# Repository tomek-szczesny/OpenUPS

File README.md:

# OpenUPS

A universal and versatile high power SBC UPS

## Introduction

**This is a work in progress repository**

More up-to-date information available on Odroid forum:

[Open source UPS design - ODROID](https://forum.odroid.com/viewtopic.php?f=55&t=46481)

License:

### Install
```
  git clone https://github.com/tomek-szczesny/OpenUPS.git

```

### OpenUPS Features:
-  Multi SBC support
-  Wide Input Voltage Range: 12V - 24V
-  Multiple Output Voltages: 5V, 12V, Programmable (0-24V) or Vin repeater,
-  Dual SATA power ports, supports 3.5" HDDs as well,
-  Dual 12V Fan ports with PWM control and RPM monitoring,
-  I2C Configuration and Reporting, incl. Battery Voltage, Current
-  3D-printable Custom Cases
   - Drive Bay Case Mount
   - Standalone Case
-  Expandable 3S1P Battery Capacity
-  18650, 20700 or 21700 Cell Support
-  Easy Battery Maintenance

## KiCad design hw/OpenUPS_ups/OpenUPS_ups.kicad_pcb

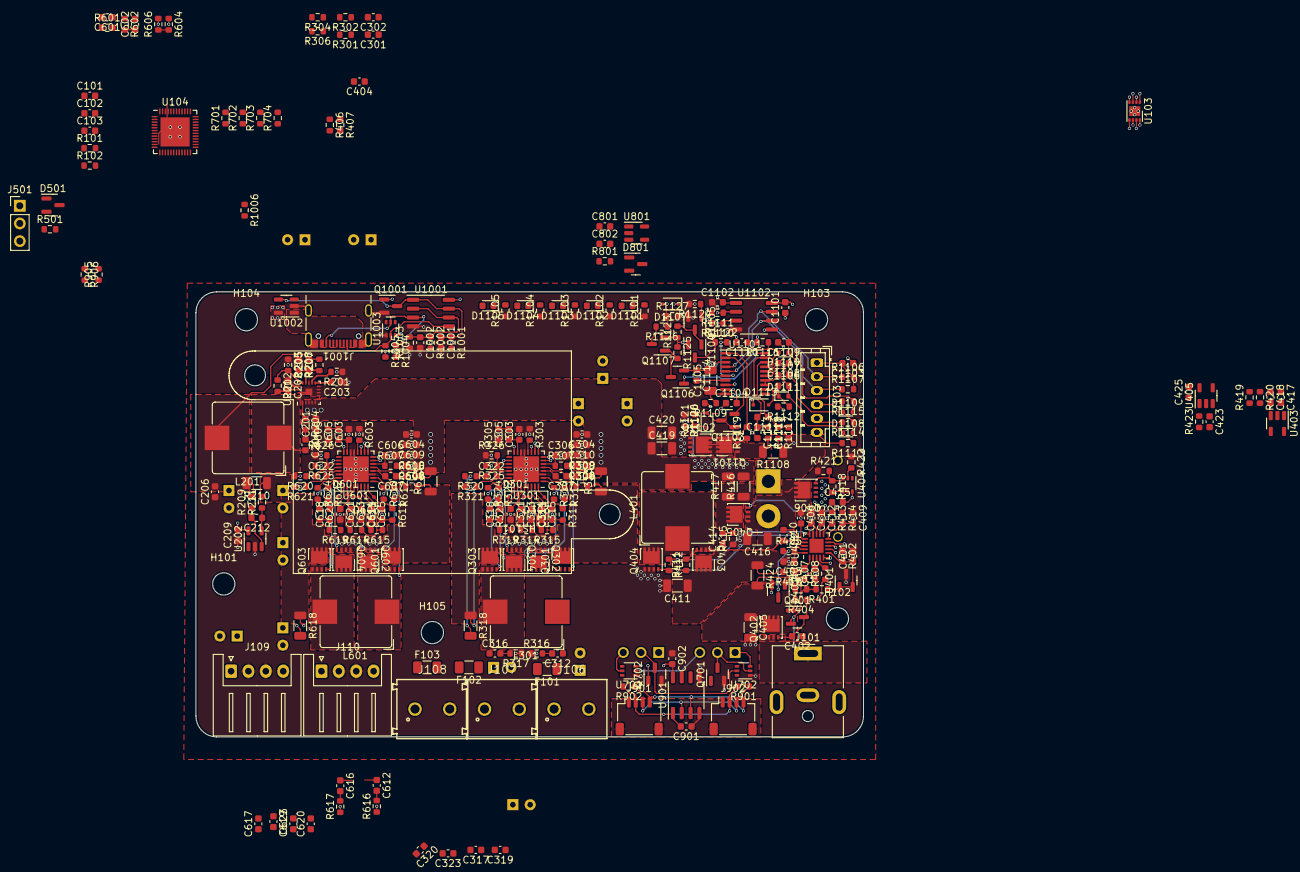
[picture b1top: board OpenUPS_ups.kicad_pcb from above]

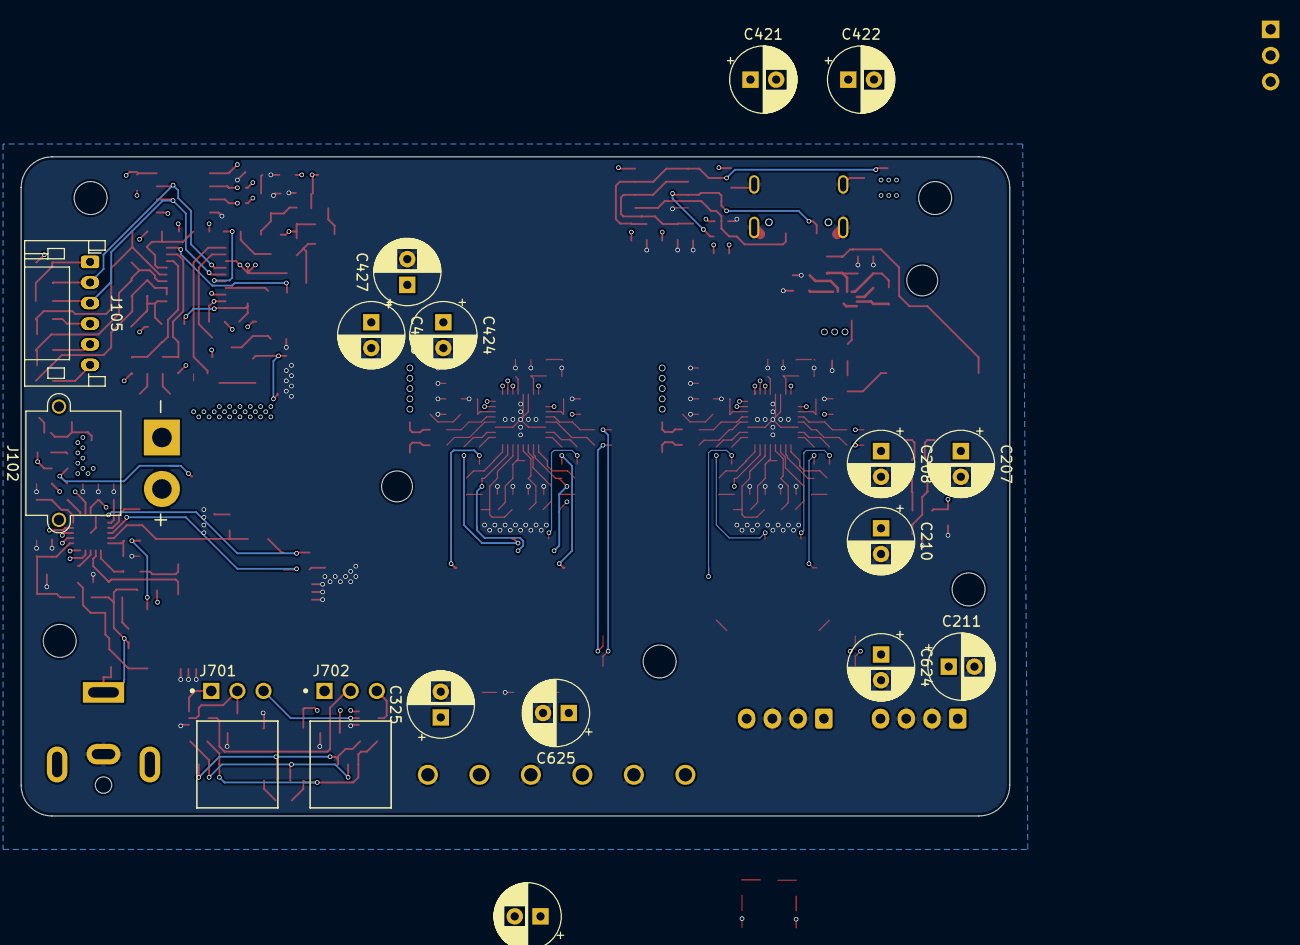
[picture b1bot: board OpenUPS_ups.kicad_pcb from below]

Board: 4 copper layers, 96.0 x 64.0 mm, 332 parts (17 on the bottom side), 182 nets.

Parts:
C101, C102, C103, C206, C209, C311, C318, C417, C425, C611, C618: 100n 10V; C_0603_1608Metric
C201, C204: 100n 50V; C_0603_1608Metric
C202, C802: 1u; C_0603_1608Metric
C203, C312, C316, C414, C612, C616, C1001: NM; C_0603_1608Metric
C205: 100p; C_0603_1608Metric
C207, C208, C210, C211: 16ZLG47MEFC6.3X7; CP_Radial_D6.3mm_P2.50mm
C212: 10u; C_0603_1608Metric
C301, C302, C307, C322, C601, C602, C607, C622, C1002: 10n; C_0603_1608Metric
C303, C603: 10p; C_0603_1608Metric
C304, C308, C309, C310, C317, C319, C320, C323, C604, C608, C609, C610, C617, C619, C620, C623: 10u 35V; C_0603_1608Metric
C305, C605: 1n5; C_0603_1608Metric
C306, C321, C606, C621: 100n 35V; C_0603_1608Metric
C313, C314, C315, C613, C614, C615: 1u 6.3V; C_0603_1608Metric
C324, C325, C421, C422, C424, C426, C427, C624, C625: 25ZLG47MEFC6.3X7; CP_Radial_D6.3mm_P2.50mm
C401: 100p 25V; C_0603_1608Metric
C402, C415: 10n 16V; C_0603_1608Metric
C403, C406, C801: 1u 25V; C_0603_1608Metric
C404: 4n7 6.3V; C_0603_1608Metric
C405: 22u 25V; C_1206_3216Metric
C407, C412, C413: 100n 25V; C_0603_1608Metric
C408, C409, C1104, C1114: 1u 16V; C_0603_1608Metric
C410: 100n 16V; C_0603_1608Metric
C411: 10u 25V; C_1206_3216Metric
C416, C1105: 10u 16V; C_1206_3216Metric
C418: 1n 10V; C_0603_1608Metric
C419, C420: 22u 16V; C_1206_3216Metric
C423, C901, C902, C1101, C1102, C1111, C1112, C1113: 100n; C_0603_1608Metric
C1103: 4u7 6.3V; C_0603_1608Metric
C1106, C1107, C1108, C1109, C1110: 1u 10V; C_0603_1608Metric
D301, D303, D601, D603, D1106, D1107, D1113: BAT54J; D_SOD-323F
D401, D801: BAT54C; SOT-23
D501: BAT54; SOT-23
D1101, D1102, D1103, D1104: G; LED_0603_1608Metric
D1105: R; LED_0603_1608Metric
D1108, D1109, D1110, D1111: ESD5Z5V0-DIO; D_SOD-523
F101, F102: C1T-4; Fuse_1206_3216Metric
F103: C1T-5; Fuse_1206_3216Metric
H101, H102, H103, H104, H105: MountingHole; MountingHole_3.2mm_M3_DIN965
HS101: Heatsink; C4_heatsink
J101: Barrel Jack; BarrelJack_CUI_PJ-063AH_Horizontal
J102: XT30PW-M; AMASS_XT30PW-M_1x02_P2.50mm_Horizontal
J103: B6B-PH-K_1x06; JST_PH_B6B-PH-K_1x06_P2.00mm_Vertical
J105: S6B-PH-K_1x06; JST_PH_S6B-PH-K_1x06_P2.00mm_Horizontal
J106, J107, J108: Screw Terminal; 691213710002
J109, J110: JST XH; JST_XH_S4B-XH-A_1x04_P2.50mm_Horizontal
J501: Conn_01x03; PinHeader_1x03_P2.54mm_Vertical
J701, J702: 0022053031; Molex-22-05-3031-MFG
J901, J902: Qwiic; JST_SH_SM04B-SRSS-TB_1x04-1MP_P1.00mm_Horizontal
J1001: USB4105-GF-A; USB_C_Receptacle_GCT_USB4105-xx-A_16P_TopMnt_Horizontal
L201, L401: SRP1038C-2R2M; L_Bourns_SRP1038C_10.0x10.0mm
L301, L601: SRP1038C-3R3M; L_Bourns_SRP1038C_10.0x10.0mm
Q301, Q302, Q303, Q304, Q402, Q403, Q404, Q405, Q601, Q602, Q603, Q604, Q1101, Q1102: AON7534; DFN 3x3 MOSFET
Q401, Q701, Q702, Q1001, Q1105, Q1106: 2N7002; SOT-23
Q406: AON7423; DFN 3x3 MOSFET
Q1103, Q1104, Q1107: BSS84; SOT-23
R101, R102, R901, R902, R905, R906, R1106, R1107: 3k3; R_0603_1608Metric
R201, R301, R302, R304, R306, R406, R407, R601, R602, R604, R606, R701, R702, R703, R704, R801, R1001, R1004, R1005, R1006, R1126, R1127: 10k; R_0603_1608Metric
R202: 330k; R_0603_1608Metric
R203, R208: 15k; R_0603_1608Metric
R204, R307, R311, R312, R319, R322, R323, R411, R412, R607, R611, R612, R619, R622, R623: 0R; R_0603_1608Metric
R207: 110k; R_0603_1608Metric
R209, R211, R310, R324, R610, R624: 3R3; R_0603_1608Metric
R210: 2mR 1206; R_1206_3216Metric
R303, R603: ?; R_0603_1608Metric
R305, R605: 20k; R_0603_1608Metric
R308, R309, R314, R320, R321, R405, R410, R608, R609, R614, R620, R621: 10R; R_0603_1608Metric
R313, R318, R613, R618: 5m 1W; R_1206_3216Metric
R315, R615: 1R; R_0603_1608Metric
R316, R317, R415, R418, R616, R617, R1110, R1111: NM; R_0603_1608Metric
R325, R401, R625, R1002: 18k; R_0603_1608Metric
R326, R626: 2k; R_0603_1608Metric
R402: 4k7; R_0603_1608Metric
R403: 3M; R_0603_1608Metric
R404, R1119, R1120, R1121: 1M; R_0603_1608Metric
R408: 5k1; R_0603_1608Metric
R413, R414: 510R; R_0603_1608Metric
R416, R417: 10m 1/2W; R_1206_3216Metric
R419: 1M2; R_0603_1608Metric
R420: 300k; R_0603_1608Metric
R421, R422, R1123, R1124, R1125: 100k; R_0603_1608Metric
R423, R1101, R1102, R1103, R1104, R1105: 1k; R_0603_1608Metric
R424: 20m 1/2W; R_1206_3216Metric
R501: 470; R_0603_1608Metric
R1003: 22k; R_0603_1608Metric
R1108: Rsns; R_1206_3216Metric
R1109: 100R; R_0603_1608Metric
R1112, R1113, R1114, R1115, R1116: 51R; R_0603_1608Metric
R1117, R1118: 100; R_0603_1608Metric
R1122: 68k; R_0603_1608Metric
U103: LM75BTP,147; SON-8-1EP_3x2mm_P0.5mm_EP1.4x1.6mm
U104: AVR64DB48x-x6LX; QFN-48-1EP_6x6mm_P0.4mm_EP4.2x4.2mm
U201: TPS51397A; Texas-VQFN-HR-20_EP_3x3_Pitch0.45mm
U202: INA180A3; SOT-23-5
U301, U601: NCP81599; QFN-32-1EP_5x5mm_P0.5mm_EP3.7x3.7mm
U401: NCP431; SOT-23
U402: BD99950; QFN-20-1EP_3.5x3.5mm_P0.5mm_EP2x2mm
U403: MCP6001R; SOT-23-5
U404: DZDH0401DW; SOT-363_SC-70-6
U405: INA180A1; SOT-23-5
U701, U702, U1003: NUP2301MW6T1G; SOT-363_SC-70-6
U801: AP7383-33W5; SOT-23-5
U901, U1102: π220N31; SO-8_3.9x4.9mm_P1.27mm
U1001: MCP6547; SO-8_3.9x4.9mm_P1.27mm
U1002: AP22814BW5; SOT-23-5
U1101: BQ76920PW; TSSOP-20_4.4x6.5mm_P0.65mm

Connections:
+3.3VA: C101.1, C102.1, C103.1, C209.2, C417.2, C425.2, C802.2, C902.2, C1102.2, D1107.1 (K), R101.2, R102.2, R306.2, R406.2, R407.2, R606.2, R701.2, R702.2, R703.2, R704.2, R905.2, R906.2, R1110.2, R1111.2, U103.8 (+Vs), U104.14 (VDDIO2), U104.28 (AVDD), U104.42 (VDD), U202.5 (V+), U403.2 (V+), U405.5 (V+), U701.3, U801.5 (VOUT), U901.8 (VDD2), U1102.1 (VDD1)
+5V: C207.1, C208.1, C210.1, C211.1, F103.1, J109.1, J110.1, R210.1, R211.2, R1001.2, R1002.2, R1004.2, R1005.2, U1001.8 (V+), U1002.5 (IN), U1003.3
+12V: C617.1, C619.1, C620.1, C623.1, C624.1, C625.1, F102.1, J109.4, J110.4, J701.1, J702.1, R618.2, R619.2, R620.2, R625.2, U702.3
+AdjV: C317.1, C319.1, C320.1, C323.1, C324.1, C325.1, F101.1, R318.2, R319.2, R320.2, R325.2
+BATT: C415.2, C416.1, C1104.2, J102.2, Q405.1 (S), Q405.2 (S), Q405.3 (S), Q406.5 (D), Q406.6 (D), Q406.7 (D), Q406.8 (D), Q1104.2 (S), Q1107.2 (S), R414.1, R419.2, R1109.2, R1112.2, R1123.1, R1125.1, U404.6 (D), U1101.9 (REGSRC)
-BATT: C1101.1, C1103.1, C1104.1, C1105.2, C1109.2, C1110.2, C1112.1, C1113.2, C1114.1, J102.1, Q1103.1 (G), Q1106.2 (S), R1108.1, R1116.2, R1117.2, U1101.3 (VSS), U1102.5 (GND2)
/12V Buck_Boost/VDRV: C614.1, D601.2 (A), D603.2 (A), R615.2, U601.29 (VDRV)
/Adj_Buck_Boost/VDRV: C314.1, D301.2 (A), D303.2 (A), R315.2, U301.29 (VDRV)
/Aux Power Supplies/EN2: C411.1, D801.1, Q403.5 (D), Q403.6 (D), Q403.7 (D), Q403.8 (D), R410.2, R424.1
/BMS/BMS_SCL: J103.3, J105.3, R1107.1, U1101.5 (SCL), U1102.6 (SCL2)
/BMS/BMS_SDA: J103.2, J105.2, R1106.1, U1101.4 (SDA), U1102.7 (SDA2)
/BMS/TS: R1122.2, U1101.6 (TS1)
/BMS_ALERT: D1107.2 (A), R1126.1, R1127.1
/BMS_WKUP: Q1105.1 (G), R1124.1
/B_ACOK: R407.1, U402.5 (ACOK)
/B_BATTRM: R406.1, U402.4 (BATTRM)
/B_I: C423.2, R423.1
/B_IOUT: C404.2, U402.7 (IOUT)
/B_U: U403.1, U403.4 (-)
/Bat_Charger/B_SRN: C412.2, Q405.5 (D), Q405.6 (D), Q405.7 (D), Q405.8 (D), R416.1, R417.1, U402.12 (SRN), U405.3 (+)
/Ext. I2C Interface/XI2C_GND: C901.1, J901.1, J901.MP (MountPin), J902.1, J902.MP (MountPin), U901.4 (GND1)
/Ext. I2C Interface/XI2C_SCL: J901.4, J902.4, R902.1, U901.3 (SCL1)
/Ext. I2C Interface/XI2C_SDA: J901.3, J902.3, R901.1, U901.2 (SDA1)
/Ext. I2C Interface/XI2C_VCC: C901.2, J901.2, J902.2, R901.2, R902.2, U901.1 (VDD1)
/F_PWM0: Q701.1 (G), R701.1
/F_PWM1: Q702.1 (G), R702.1
/F_Tach0: J701.3, R703.1, U701.2
/F_Tach1: J702.3, R704.1, U701.5
/I2C_B_SCL: R1110.1, U104.37 (PF3), U1102.3 (SCL1)
/I2C_B_SDA: R1111.1, U104.36 (PF2), U1102.2 (SDA1)
/I2C_E_SCL: R905.1, U104.13 (PC3), U901.6 (SCL2)
/I2C_E_SDA: R906.1, U104.12 (PC2), U901.7 (SDA2)
/I2C_I_SCL: R102.1, U103.2 (SCL), U104.47 (PA3), U301.10 (SCL), U402.9 (SCL), U601.10 (SCL)
/I2C_I_SDA: R101.1, U103.1 (SDA), U104.46 (PA2), U301.9 (SDA), U402.8 (SDA), U601.9 (SDA)
/UPDI: D501.1 (A), J501.3, U104.41 (UPDI)
/USB_FORCE: Q1001.1 (G), R1006.2
/V5_EN: R201.2, U201.12 (EN)
/V5_Imon: U104.26 (PD6), U202.1
/V12_CS1: C602.1, R602.2, U104.24 (PD4), U601.7 (CS1)
/V12_CS2: C601.1, R601.2, U104.25 (PD5), U601.18 (CS2)
/V12_EN: R604.2, R606.1, U601.16 (EN)
/VC1: J103.4, J105.4, R1115.2
/VC2: J103.5, J105.5, R1114.2
/VC3: J103.6, J105.6, R1113.2
/Vadj_CS1: C302.1, R302.2, U104.22 (PD2), U301.7 (CS1)
/Vadj_CS2: C301.1, R301.2, U104.23 (PD3), U301.18 (CS2)
/Vadj_EN: R304.2, R306.1, U301.16 (EN)
GND: C101.2, C102.2, C103.2, C201.1, C202.1, C203.1, C206.1, C207.2, C208.2, C209.1, C210.2, C211.2, C301.2, C302.2, C303.2, C304.2, C306.2, C308.2, C309.2, C310.2, C313.2, C314.2, C315.2, C317.2, C319.2, C320.2, C321.2, C323.2, C324.2, C325.2, C401.2, C403.2, C404.1, C405.2, C406.1, C407.1, C409.1, C411.2, C412.1, C413.1, C416.2, C417.1, C418.1, C419.2, C420.2, C421.2, C422.2, C423.1, C424.2, C425.1, C426.2, C427.2, C601.2, C602.2, C603.2, C604.2, C606.2, C608.2, C609.2, C610.2, C613.2, C614.2, C615.2, C617.2, C619.2, C620.2, C621.2, C623.2, C624.2, C625.2, C801.1, C802.1, C902.1, C1001.2, C1002.2, C1102.1, J101.2, J106.2, J107.2, J108.2, J109.2, J109.3, J110.2, J110.3, J501.1, J1001.A1 (GND), J1001.A12 (GND), J1001.B1 (GND), J1001.B12 (GND), J1001.S1 (SHIELD), Q302.1 (S), Q302.2 (S), Q302.3 (S), Q304.1 (S), Q304.2 (S), Q304.3 (S), Q404.1 (S), Q404.2 (S), Q404.3 (S), Q602.1 (S), Q602.2 (S), Q602.3 (S), Q604.1 (S), Q604.2 (S), Q604.3 (S), Q701.2 (S), Q702.2 (S), Q1001.2 (S), Q1102.1 (S), Q1102.2 (S), Q1102.3 (S), Q1105.2 (S), R201.1, R203.1, R208.1, R301.1, R302.1, R303.1, R304.1, R305.1, R316.1, R317.1, R326.1, R402.1, R415.1, R420.1, R421.1, R422.1, R601.1, R602.1, R603.1, R604.1, R605.1, R616.1, R617.1, R626.1, R801.1, R1003.1, R1006.1, R1101.1, R1102.1, R1103.1, R1104.1, R1105.1, R1120.1, R1124.2, R1127.2, U103.4 (GND), U103.5 (A2), U103.6 (A1), U103.7 (A0), U104.15 (GND), U104.29 (AGND), U104.43 (GND), U104.49 (GND), U201.7 (PGND), U201.8 (PGND), U201.9 (PGOOD), U201.10 (NC), U201.13 (AGND), U201.16 (NC), U201.18 (PGND), U201.21 (PGND), U202.2 (GND), U301.3 (PGND1), U301.13 (AGND), U301.14 (AGND), U301.22 (PGND2), U301.33 (THPAD), U401.3 (A), U402.14 (GND), U402.21 (PAD), U403.5 (V-), U405.2 (GND), U601.3 (PGND1), U601.13 (AGND), U601.14 (AGND), U601.22 (PGND2), U601.33 (THPAD), U701.1, U702.1, U801.2 (GND), U801.4 (NC), U901.5 (GND2), U1001.4 (V-), U1002.2 (GND), U1003.1, U1102.4 (GND1)
unnamed: C204.1, R204.2
unnamed: C204.2, L201.1, U201.6 (SW), U201.19 (SW), U201.20 (SW)
unnamed: C205.2, C206.2, L201.2, R207.2, R209.2, R210.2
unnamed: C305.2, R305.2
unnamed: C311.1, R311.2
unnamed: C312.2, R316.2
unnamed: C316.2, R317.2
unnamed: C318.1, R323.2
unnamed: C414.2, R415.2
unnamed: C605.2, R605.2
unnamed: C611.1, R611.2
unnamed: C612.2, R616.2
unnamed: C616.2, R617.2
unnamed: C618.1, R623.2
unnamed: D301.1 (K), R323.1, U301.25 (BST2)
unnamed: D303.1 (K), R311.1, U301.32 (BST1)
unnamed: D401.3, R405.1
unnamed: D501.3 (K), R501.1
unnamed: D601.1 (K), R623.1, U601.25 (BST2)
unnamed: D603.1 (K), R611.1, U601.32 (BST1)
unnamed: D1101.1 (K), R1101.2
unnamed: D1102.1 (K), R1102.2
unnamed: D1103.1 (K), R1103.2
unnamed: D1104.1 (K), R1104.2
unnamed: D1105.1 (K), R1105.2
unnamed: D1106.2 (A), Q1103.3 (D), R1121.2
unnamed: D1106.1 (K), Q1102.4 (G), R1120.2, R1121.1
unnamed: C1106.2, C1107.1, D1108.1 (A1), D1111.2 (A2), R1113.1, U1101.13 (VC4), U1101.14 (VC3)
unnamed: C1107.2, C1108.1, D1108.2 (A2), D1109.1 (A1), R1114.1, U1101.15 (VC2)
unnamed: C1108.2, C1109.1, D1109.2 (A2), D1110.1 (A1), R1115.1, U1101.16 (VC1)
unnamed: C1110.1, D1110.2 (A2), R1116.1, U1101.17 (VC0)
unnamed: C1106.1, D1111.1 (A1), D1113.2 (A), R1112.1, U1101.12 (VC5)
unnamed: C1105.1, D1113.1 (K), R1109.1, U1101.10 (BAT)
unnamed: F101.2, J106.1
unnamed: F102.2, J107.1
unnamed: F103.2, J108.1
unnamed: J501.2, R501.2
unnamed: J701.2, Q701.3 (D), U702.2
unnamed: J702.2, Q702.3 (D), U702.5
unnamed: J1001.A5 (CC1), R1005.1, U1001.5 (+), U1003.2
unnamed: J1001.B5 (CC2), R1004.1, U1001.3 (+), U1003.5
unnamed: Q301.5 (D), Q301.6 (D), Q301.7 (D), Q301.8 (D), R309.2, R313.1
unnamed: Q301.4 (G), R310.2
unnamed: Q302.4 (G), R312.2
unnamed: Q303.5 (D), Q303.6 (D), Q303.7 (D), Q303.8 (D), R318.1, R321.2
unnamed: Q303.4 (G), R322.2
unnamed: Q304.4 (G), R324.2
unnamed: C402.2, Q401.3 (D), Q402.4 (G), R404.1, R408.1
unnamed: Q401.1 (G), R403.1, R404.2
unnamed: Q403.4 (G), R411.2
unnamed: Q404.4 (G), R412.2
unnamed: C415.1, Q405.4 (G), R413.1
unnamed: Q406.4 (G), R418.1, R421.2, U404.3 (BIAS)
unnamed: Q601.5 (D), Q601.6 (D), Q601.7 (D), Q601.8 (D), R609.2, R613.1
unnamed: Q601.4 (G), R610.2
unnamed: Q602.4 (G), R612.2
unnamed: Q603.5 (D), Q603.6 (D), Q603.7 (D), Q603.8 (D), R618.1, R621.2
unnamed: Q603.4 (G), R622.2
unnamed: Q604.4 (G), R624.2
unnamed: C1001.1, Q1001.3 (D), R1001.1, U1001.1, U1001.7, U1002.4 (~EN)
unnamed: Q1101.5 (D), Q1101.6 (D), Q1101.7 (D), Q1101.8 (D), Q1102.5 (D), Q1102.6 (D), Q1102.7 (D), Q1102.8 (D)
unnamed: Q1101.4 (G), R1119.2, U1101.1 (DSG)
unnamed: Q1101.1 (S), Q1101.2 (S), Q1101.3 (S), R1108.2, R1118.2, R1119.1
unnamed: Q1103.2 (S), U1101.2 (CHG)
unnamed: Q1104.3 (D), R1122.1
unnamed: Q1104.1 (G), Q1105.3 (D), R1123.2
unnamed: Q1106.3 (D), Q1107.1 (G), R1125.2
unnamed: Q1106.1 (G), U1101.20 (ALERT)
unnamed: Q1107.3 (D), R1126.2
unnamed: R423.2, U405.1
unnamed: R204.1, U201.1 (BST)
unnamed: C205.1, R207.1, R208.2, U201.14 (FB)
unnamed: R202.1, R203.2, U201.15 (MODE)
unnamed: C203.2, U201.11 (SS)
unnamed: C202.2, R202.2, U201.17 (VCC)
unnamed: C212.2, R209.1, U202.3 (+)
unnamed: C212.1, R211.1, U202.4 (-)
unnamed: R303.2, U301.12 (ADDR)
unnamed: C303.1, C305.1, U301.15 (COMP)
unnamed: C315.1, R314.1, R315.1, U301.30 (VCC)
unnamed: C313.1, R314.2, U301.28 (VCCD)
unnamed: C307.2, R309.1, U301.4 (CSN1)
unnamed: C307.1, R308.1, U301.5 (CSP1)
unnamed: R310.1, U301.1 (HSG1)
unnamed: R312.1, U301.2 (LSG1)
unnamed: C306.1, R307.1, U301.6 (V1)
unnamed: C311.2, C312.1, L301.1, Q301.1 (S), Q301.2 (S), Q301.3 (S), Q302.5 (D), Q302.6 (D), Q302.7 (D), Q302.8 (D), U301.31 (VSW1)
unnamed: C322.1, R320.1, U301.20 (CSN2)
unnamed: C322.2, R321.1, U301.21 (CSP2)
unnamed: R325.1, R326.2, U301.19 (FB)
unnamed: R322.1, U301.24 (HSG2)
unnamed: R324.1, U301.23 (LSG2)
unnamed: C321.1, R319.1, U301.27 (V2)
unnamed: C316.1, C318.2, L301.2, Q303.1 (S), Q303.2 (S), Q303.3 (S), Q304.5 (D), Q304.6 (D), Q304.7 (D), Q304.8 (D), U301.26 (VSW2)
unnamed: C401.1, R401.1, R402.2, U401.1 (REF), U401.2 (K), U402.6 (ACDET)
unnamed: R408.2, U402.3 (ACGATE)
unnamed: C408.2, R410.1, U402.1 (ACN)
unnamed: C405.1, C407.2, C408.1, Q402.5 (D), Q402.6 (D), Q402.7 (D), Q402.8 (D), R424.2, U402.2 (ACP)
unnamed: C409.2, R414.2, U402.10 (BATT)
unnamed: R413.2, U402.11 (BGATE)
unnamed: C410.1, U402.17 (BOOT)
unnamed: R411.1, U402.18 (HDRV)
unnamed: R412.1, U402.15 (LDRV)
unnamed: C410.2, C414.1, L401.1, Q403.1 (S), Q403.2 (S), Q403.3 (S), Q404.5 (D), Q404.6 (D), Q404.7 (D), Q404.8 (D), U402.19 (PHASE)
unnamed: C406.2, U402.16 (REGN)
unnamed: C403.1, R405.2, U402.20 (VCC)
unnamed: C418.2, R419.1, R420.2, U403.3 (+)
unnamed: R422.2, U404.2 (REF)
unnamed: R603.2, U601.12 (ADDR)
unnamed: C603.1, C605.1, U601.15 (COMP)
unnamed: C615.1, R614.1, R615.1, U601.30 (VCC)
unnamed: C613.1, R614.2, U601.28 (VCCD)
unnamed: C607.2, R609.1, U601.4 (CSN1)
unnamed: C607.1, R608.1, U601.5 (CSP1)
unnamed: R610.1, U601.1 (HSG1)
unnamed: R612.1, U601.2 (LSG1)
unnamed: C606.1, R607.1, U601.6 (V1)
unnamed: C611.2, C612.1, L601.1, Q601.1 (S), Q601.2 (S), Q601.3 (S), Q602.5 (D), Q602.6 (D), Q602.7 (D), Q602.8 (D), U601.31 (VSW1)
unnamed: C622.1, R620.1, U601.20 (CSN2)
unnamed: C622.2, R621.1, U601.21 (CSP2)
unnamed: R625.1, R626.2, U601.19 (FB)
unnamed: R622.1, U601.24 (HSG2)
unnamed: R624.1, U601.23 (LSG2)
unnamed: C621.1, R619.1, U601.27 (V2)
unnamed: C616.1, C618.2, L601.2, Q603.1 (S), Q603.2 (S), Q603.3 (S), Q604.5 (D), Q604.6 (D), Q604.7 (D), Q604.8 (D), U601.26 (VSW2)
unnamed: D801.3, R801.2, U801.3 (EN)
unnamed: C1002.1, R1002.1, R1003.2, U1001.2 (-), U1001.6 (-)
unnamed: J1001.A4 (VBUS), J1001.A9 (VBUS), J1001.B4 (VBUS), J1001.B9 (VBUS), U1002.1 (OUT)
unnamed: C1114.2, U1101.7 (CAP1)
unnamed: C1111.2, C1113.1, R1118.1, U1101.19 (SRN)
unnamed: C1111.1, C1112.2, R1117.1, U1101.18 (SRP)
VBMS: C1101.2, C1103.2, J103.1, J105.1, R1106.2, R1107.2, U1101.8 (REGOUT), U1102.8 (VDD2)
Vin: C402.1, D401.1, J101.1, Q401.2 (S), Q402.1 (S), Q402.2 (S), Q402.3 (S), R401.2, R403.2
Vsys: C201.2, C304.1, C308.1, C309.1, C310.1, C413.2, C419.1, C420.1, C421.1, C422.1, C424.1, C426.1, C427.1, C604.1, C608.1, C609.1, C610.1, C801.2, D401.2, L401.2, Q406.1 (S), Q406.2 (S), Q406.3 (S), R307.2, R308.2, R313.2, R416.2, R417.2, R418.2, R607.2, R608.2, R613.2, U201.2 (VIN), U201.3 (VIN), U201.4 (VIN), U201.5 (VIN), U402.13 (SRP), U404.4 (S), U405.4 (-), U801.1 (VIN)

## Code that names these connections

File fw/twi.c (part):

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        // set twi pin mux
        switch(twi_bus->pins) {
            case TWI_PINS_ALT1 :
                PORTMUX_TWIROUTEA = PORTMUX_TWI0_ALT1_gc;   /* PA2, PA3, PC6, PC7 */
                PORTA_DIRSET = PIN2_bm | PIN3_bm;
                if(twi_bus->pullup == true) PORTA_PINCONFIG = PORT_PULLUPEN_bm;
                PORTA_PINCTRLUPD = PIN2_bm | PIN3_bm;
            case TWI_PINS_ALT2 :
                PORTMUX_TWIROUTEA = PORTMUX_TWI0_ALT2_gc;   /* PC2, PC3, PC6, PC7 */
                PORTC_DIRSET = PIN2_bm | PIN3_bm;
                if(twi_bus->pullup == true) PORTC_PINCONFIG = PORT_PULLUPEN_bm;
                PORTC_PINCTRLUPD = PIN2_bm | PIN3_bm;
            case TWI_PINS_DEFAULT :
                PORTMUX_TWIROUTEA = PORTMUX_TWI0_DEFAULT_gc;    /* PA2, PA3, PC2, PC3 */
                PORTA_DIRSET = PIN2_bm | PIN3_bm;
                if(twi_bus->pullup == true) PORTA_PINCONFIG = PORT_PULLUPEN_bm;
                PORTA_PINCTRLUPD = PIN2_bm | PIN3_bm;
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        // set twi pin mux
        switch(twi_bus->pins) {
            case TWI_PINS_ALT1 :
                PORTMUX_TWIROUTEA = PORTMUX_TWI1_DEFAULT_gc;   /* PF2, PF3 */
                PORTF_DIRSET = PIN2_bm | PIN3_bm;
                if(twi_bus->pullup == true) PORTF_PINCONFIG = PORT_PULLUPEN_bm;
                PORTF_PINCTRLUPD = PIN2_bm | PIN3_bm;
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                if(twi_bus->pullup == true) PORTB_PINCONFIG = PORT_PULLUPEN_bm;
                PORTB_PINCTRLUPD = PIN2_bm | PIN3_bm;
            case TWI_PINS_DEFAULT :
                PORTMUX_TWIROUTEA = PORTMUX_TWI1_DEFAULT_gc;    /* PF2, PF3, PB2, PB3 */
                PORTF_DIRSET = PIN2_bm | PIN3_bm;
                if(twi_bus->pullup == true) PORTF_PINCONFIG = PORT_PULLUPEN_bm;
                PORTF_PINCTRLUPD = PIN2_bm | PIN3_bm;
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
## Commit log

2023-04-21 Initial KiCAD commits
2023-04-21 More cleanups and stuff
2023-04-22 Fixed ground symbols
2023-04-22 Preliminary battery charger circuit
2023-04-22 initial commit of PCB models, updated readme.md
2023-04-22 corrected readme.md
2023-04-23 added drivebay case
2023-04-23 created terminal block screw openings and annotation
2023-04-23 Secondary blocks design
2023-04-23 code cleanup and xt60 creation
2023-04-24 mini case work
2023-04-24 more mini case refinement
2023-04-24 updated image
2023-04-24 Update OpenUPS features list
2023-04-24 Added Ideal Diode ORing solution
2023-04-24 Change minimum input voltage back to 12V
2023-04-25 Upgraded battery charger with synchronous HB Driver
2023-04-26 Battery charger HB driver changed to NCP5901
2023-04-28 created xt30 components and changed mini case to use xt30
2023-04-28 platter view created, swapped i2c and fan, more code cleanup
2023-04-28 work on 3s1p battery case
2023-04-28 work on 3s2p battery case
2023-04-28 A buildable AVR FW template
2023-04-28 Deps cleanup
2023-04-30 4th generation battery charger
2023-05-01 increased space for fan connectors
2023-05-01 External I2C isolator
2023-05-02 customizer gui added
2023-05-02 corrected staggered battery clip placement
2023-05-02 Work on Buck Boosts
2023-05-02 Work on 5V; EN pins taken care of.
2023-05-03 Added ports and fuses
2023-05-05 Issue #17
2023-05-05 Issue #13, USB-C output, at last!
2023-05-06 Issue #20: replaced AVR with 48-pin TQFP
2023-05-06 Issue #16: Added LED indicators
2023-05-07 increased 3s1p battery pcb size, adjusted drivebay case
2023-05-08 more work for battery pcb size increase and case pillars.
2023-05-09 Issue #24 5th generation charger (may need some tuning)
2023-05-10 xt30 orientation change and additional foot prints for all pcb, added 3s1p pcb dxf drawing, updated image
2023-05-10 Issue #24 - battery charger, good for review
2023-05-12 added header interconnect, arranged battery connctors, led, usb-c and other changes
2023-05-12 created dxf file for ups and 3s2p pcb, updated openups_pcb.png
2023-05-13 Revert "work on 3s2p battery case"
    This reverts commit d35319efd431c702fc1be0438e49ec9e5fffffa4.
2023-05-13 Revert "work on 3s1p battery case"
    This reverts commit 1a45b3675fc5b00893d7b6622b8964d1ce6814fb.
2023-05-13 Revert "created xt30 components and changed mini case to use xt30"
    This reverts commit ccc60c90d4db5fe0236a61b43db1235a52bc742a.
2023-05-13 Revert "platter view created, swapped i2c and fan, more code cleanup"
    This reverts commit 2f2f817d291441a83b86ed38aa68c17b6ac24d99.
2023-05-13 Revert "Change minimum input voltage back to 12V"
    This reverts commit 13d1a0fb0a5e56c0f9c625028acc5f1636d0e2bc.
2023-05-13 Revert "Update OpenUPS features list"
    This reverts commit 6bbaafdd772efd2edaa44b149d43046b53483c6d.
2023-05-13 Revert "updated image"
    This reverts commit c952793fde73713bad661229f0cd12625c9fa447.
2023-05-13 Revert "more mini case refinement"
    This reverts commit a3ebdb0b7108780deea73706272cdddaaeca8788.
2023-05-13 Revert "mini case work"
    This reverts commit 137acbc8cbf3d331e2e1506e5e7c8241f24b06a2.
2023-05-13 Revert "code cleanup and xt60 creation"
    This reverts commit 32258280bedffabc0b83e3cba687f16b202a1598.
2023-05-14 Preliminary NMOS: AON7534; USB-C selected.
2023-05-14 Added battery data link (connectors TBC)
2023-05-14 Removed Vref (AVR has its own). Replaced INA181s with INA180s
2023-05-14 Initial placement effort
2023-05-15 moved pcb hole, xt30, fixed sata connectors, fixed heatsink hole, moved terminal blocksand fixed xt30pw-m model.
2023-05-15 Layout: Component models, mechanical, connectors
2023-05-15 added debug mode
2023-05-16 Replaced polyfuses with 1206 fuses #12
2023-05-16 Added 3D models from @hominoid
2023-05-16 Unified sense resistors to 10mR; Placement
2023-05-17 adjusted xt30pw-m footprint
2023-05-17 Added inductor 3D models
2023-05-17 Updated XT30 model
2023-05-17 more xt30pw-m refinements
2023-05-18 The final update of XT30 model. :)
2023-05-19 Issue #30: USB Force ON feature
2023-05-19 Issue #22 ESD protection on USB, Bat Data, Fans
2023-05-19 Issue #23: Thin BAT54 diodes in converters
2023-05-19 Issue #23: Added thermal sensor
2023-05-19 xt30pw-f adjustments
2023-05-19 12V converter layout
2023-05-20 Applied design rules to PCB editor #28
2023-05-21 Update of XT30 3D models
2023-05-21 Converter placement
2023-05-21 Layout WIP
2023-05-21 PCB placement
2023-05-22 Extra large transistor copper pours
2023-05-24 Introducing reverse polarity protected adapter voltage
2023-05-25 Charger layout
2023-05-25 updated firmware makefile, add blink routine for toolchain testing on hardware.
2023-05-28 added twi.c, twi.h AVR Dx I2C initialization routine that supports both TWI0 and TWI1 in either host or client mode.
2023-05-28 fixed typos in twi.c and twi.h
2023-05-28 Added the fifth mounting hole
2023-05-28 More charger layout
2023-05-29 updated ups pcb hole and component locations and the drvebay and mini cases, add thekicad 3d ups pcb model to the gui.
2023-06-02 created ic headers and assets directory, updated readme.md
2023-06-04 increased ups pcb size to 96 x 64, moved holes and updaed cases
2023-06-04 updated system diagram, adjusted mount hole and projection code.
2023-06-06 PCB enlarged; 4 holes, LEDs and USB moved; two keepouts;
2023-06-06 Preliminary BMS circuit (not done yet)
2023-06-08 added dual mode, smart mode, pin mux select and other bits to twi_init()
2023-06-08 Issue #35 - AVR changed to VQFN 48-pin
2023-06-08 Some work on BMS
2023-06-09 added struct twi_bus in twi_init() to hold bus options for each port passed as a pointer.
2023-06-09 set -ml to enable math lib in linker
2023-06-10 BMS work
2023-06-11 BMS implementation complete (on schematic)
2023-06-14 PCB multitasking
2023-06-20 BMS placement complete (no routing)
2023-06-21 Batt charger placement
2023-06-24 East Side layout and routing
2023-06-29 A footprint for TPS25947
2023-07-02 added twi_start(), twi_wait(), twi_read_poll(), twi_write_poll(), twi_read_reg()
2023-07-02 restructured directory layout and added mcp9808 tempature sensor driver.
2023-07-04 fixed system clk and SCL clk hold, expanded twi_bus structure, replaced baud rate function.

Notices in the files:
fw/twi.c:
Copyright (c) 2023 Edward Kisiel hominoid@cablemi.com All rights reserved.
LICENSE: GNU GPLv3
